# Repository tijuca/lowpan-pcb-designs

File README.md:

# lowpan-pcb-designs
Collection of PCB designs mainly for 6LoWPAN hardware

Note that all projects and files are 'Open Source' under the terms of the
definition for Open Source Hardware Association.

http://www.oshwa.org/definition/

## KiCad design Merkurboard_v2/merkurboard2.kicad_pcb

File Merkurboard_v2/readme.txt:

# merkurboard2.pro #
####################

This folder contains a KiCad project named 'merkurboard2'.
Open the file merkurboard.pro with the KiCad project manager to open than the
schematic and/or the PCB layout.

The original Merkurboard (version 1) was created by the gyus from OSDomotics.
This folder simply contains the recreated schematic and a new PCB layout based
on the original files and data from OSDomotics by the KiCad EDA suite.

http://kicad-pcb.org/

The PCB layout is also uploaded to the services of OSH Park.

https://oshpark.com/

You can find and order a prepared PCB project on OSH Park on the following URL:

https://oshpark.com/shared_projects/iTdx3rUN

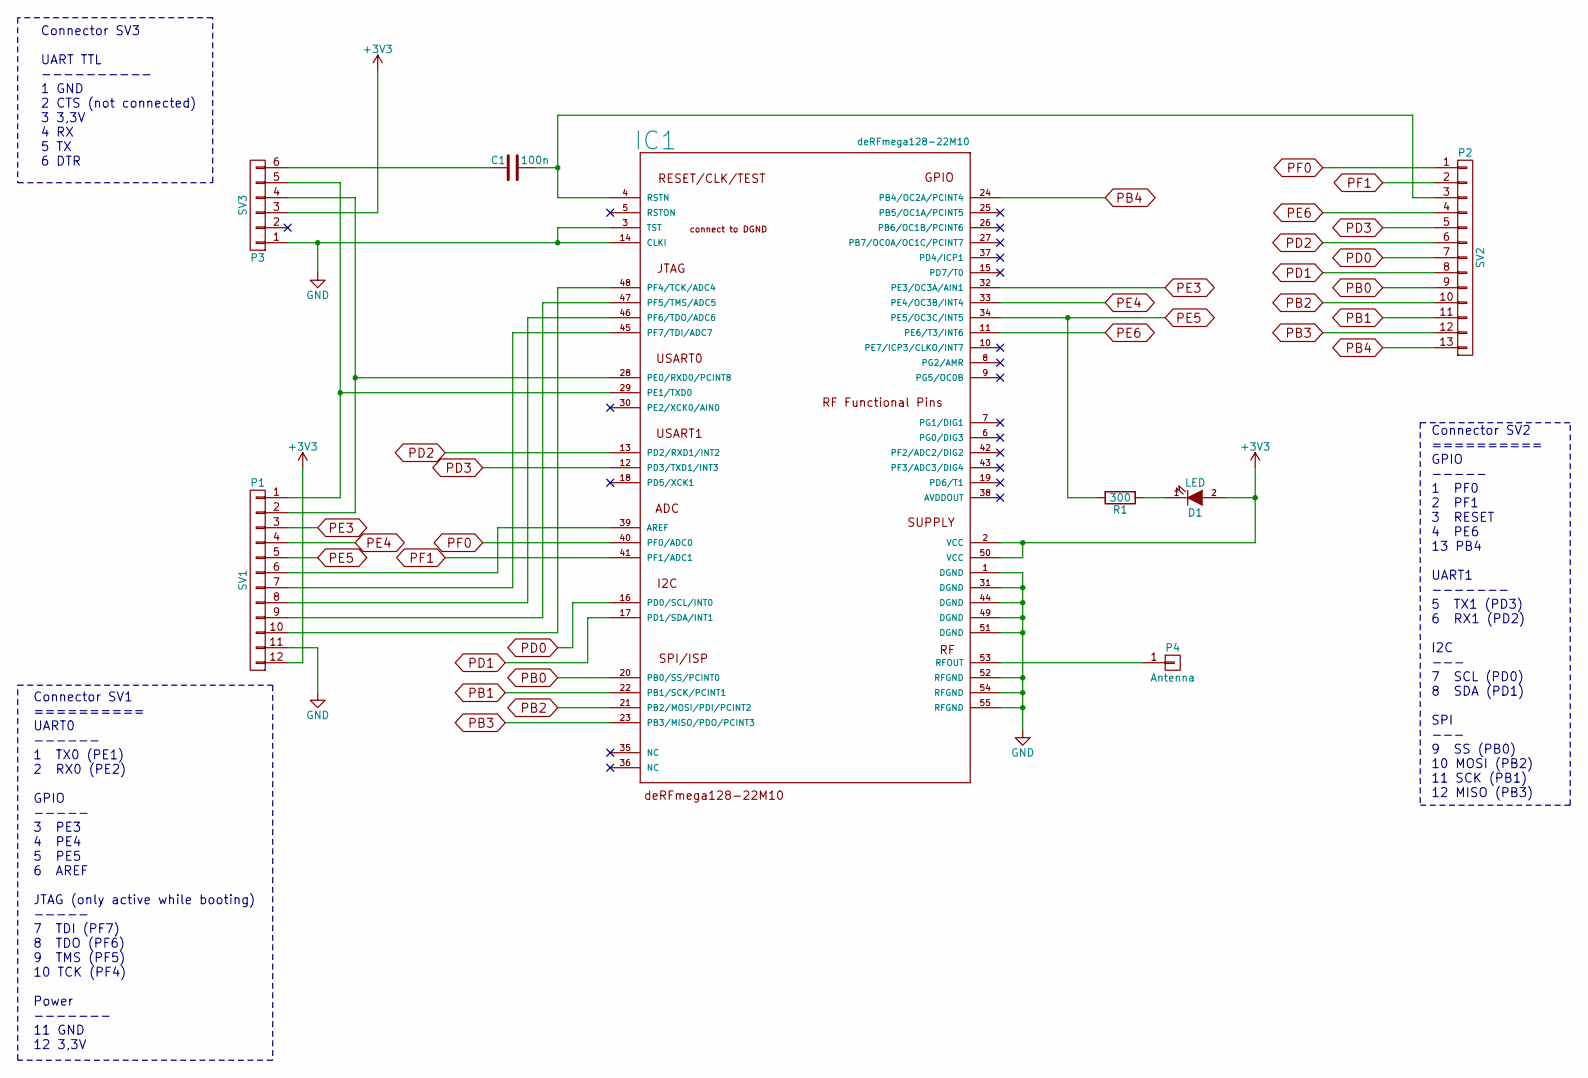
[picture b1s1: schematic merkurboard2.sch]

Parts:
C1: 100n; C_0603
D1: LED; LED_0603
IC1: deRFmega128-22M10; A-M10
P1: SV1; Pin_Header_Straight_1x12
P2: SV2; Pin_Header_Straight_1x13
P3: SV3; Pin_Header_Straight_1x06
P4: Antenna; Pin_Header_Straight_1x01
R1: 300; R_0603

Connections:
+3V3: D1.2 (A), IC1.2 (VCC), IC1.50 (VCC), P1.12, P3.3
GND: IC1.1 (DGND), IC1.3 (TST), IC1.14 (CLKI), IC1.31 (DGND), IC1.44 (DGND), IC1.49 (DGND), IC1.51 (DGND), IC1.52 (RFGND), IC1.54 (RFGND), IC1.55 (RFGND), P1.11, P3.1
unnamed: C1.1, IC1.4 (RSTN), P2.3
unnamed: C1.2, P3.6
unnamed: D1.1 (K), R1.1
unnamed: IC1.28 (PE0/RXD0/PCINT8), P1.2, P3.4
unnamed: IC1.29 (PE1/TXD0), P1.1, P3.5
unnamed: IC1.39 (AREF), P1.6
unnamed: IC1.45 (PF7/TDI/ADC7), P1.7
unnamed: IC1.46 (PF6/TDO/ADC6), P1.8
unnamed: IC1.47 (PF5/TMS/ADC5), P1.9
unnamed: IC1.48 (PF4/TCK/ADC4), P1.10
unnamed: IC1.53 (RFOUT), P4.1
PB0: IC1.20 (PB0/SS/PCINT0), P2.9
PB1: IC1.22 (PB1/SCK/PCINT1), P2.11
PB2: IC1.21 (PB2/MOSI/PDI/PCINT2), P2.10
PB3: IC1.23 (PB3/MISO/PDO/PCINT3), P2.12
PB4: IC1.24 (PB4/OC2A/PCINT4), P2.13
PD0: IC1.16 (PD0/SCL/INT0), P2.7
PD1: IC1.17 (PD1/SDA/INT1), P2.8
PD2: IC1.13 (PD2/RXD1/INT2), P2.6
PD3: IC1.12 (PD3/TXD1/INT3), P2.5
PE3: IC1.32 (PE3/OC3A/AIN1), P1.3
PE4: IC1.33 (PE4/OC3B/INT4), P1.4
PE5: IC1.34 (PE5/OC3C/INT5), P1.5, R1.2
PE6: IC1.11 (PE6/T3/INT6), P2.4
PF0: IC1.40 (PF0/ADC0), P2.1
PF1: IC1.41 (PF1/ADC1), P2.2

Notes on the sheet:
Connector SV3 UART TTL ---------- 1 GND 2 CTS (not connected) 3 3,3V 4 RX 5 TX 6 DTR
Connector SV1 ========== UART0 ------ 1 TX0 (PE1) 2 RX0 (PE2) GPIO ----- 3 PE3 4 PE4 5 PE5 6 AREF JTAG (only active while booting) ----- 7 TDI (PF7) 8 TDO (PF6) 9 TMS (PF5) 10 TCK (PF4) Power ------- 11 GND 12 3,3V
Connector SV2 ========== GPIO ----- 1 PF0 2 PF1 3 RESET 4 PE6 13 PB4 UART1 ------- 5 TX1 (PD3) 6 RX1 (PD2) I2C --- 7 SCL (PD0) 8 SDA (PD1) SPI --- 9 SS (PB0) 10 MOSI (PB2) 11 SCK (PB1) 12 MISO (PB3)

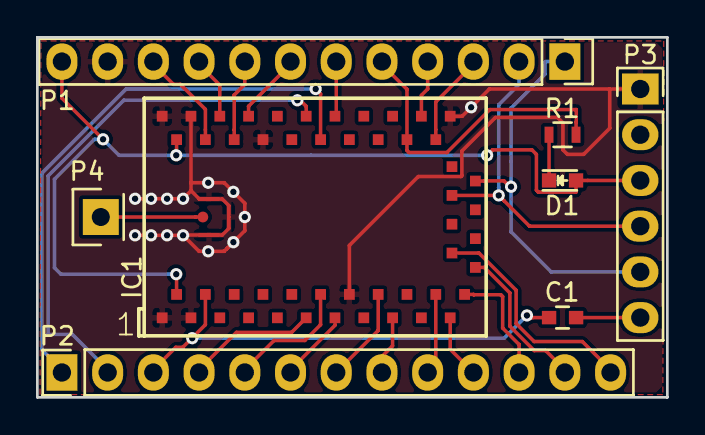
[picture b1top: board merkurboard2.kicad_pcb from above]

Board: 2 copper layers, 35.0 x 20.0 mm, 8 parts (0 on the bottom side), 28 nets.

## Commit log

2016-11-17 Adding the Merkurboard v2
2016-11-17 Adding first a default readme
2016-11-17 Updating KiCad files for the Merkurboard v2
2016-12-04 Adding 3-D model views for merkurboard_v2
